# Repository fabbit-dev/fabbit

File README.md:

<h1 align="center">
  <picture>
    <source media="(prefers-color-scheme: dark)" srcset="docs/img/fabbit-logo-dark.png">
    
  </picture>
</h1>

<p align="center">
  Открытый карманный прибор электронщика на ПЛИС, сделанный двумя школьниками.<br>
  Профиль меняет схему прибора.
</p>

<p align="center">

</p>

<p align="center">

</p>

<p align="center">
  <sub>сайт <a href="https://fabbit.dev">fabbit.dev</a></sub>
</p>

## Что это

Fabbit собирает в одном корпусе логический анализатор (ЛА), отладчик, осциллограф,
генератор, мультиметр и лабораторный источник. На экране и по HDMI идут ретро-игры.

Внутри модуль ПЛИС Artix-7. Профиль — битстрим ПЛИС с логикой прибора, его выбирают в меню.

Fabbit для инженеров и исследователей железа. Код, платы и корпус открыты:
свой профиль или свою плату-мезонин может сделать любой.

## Профили из коробки

| Профиль | Что умеет |
|---|---|
| Логический анализатор | Порт A: 16 входов 0–10 В (выдерживают ±30 В), порог 0–6,8 В, входы CK и TRIG. Порт B: 8 двунаправленных линий 1,1–4,7 В. Поток в ПК: 50 MS/s на 16 каналах или 100 MS/s на 8 |
| Отладчик debug & trace | CMSIS-DAP v2: SWD, JTAG, trace 4 бит, разъём MIPI-20 |
| Осциллограф | 2 канала, АЦП HMCAD1511 8 бит, 2 × 312–375 MS/s, 2 × 400 MS/s после подстройки задержек LVDS, щупы ×1/×10 |
| Генератор | ЦАП DAC904 14 бит, 9,6 Впп без нагрузки, 4,8 Впп на 50 Ом. Выход выдерживает ±25 В |
| Мультиметр | АЦП ADS1220 24 бит: напряжение, сопротивление |
| Лабораторный источник | 0,8–22 В с ограничением тока: до 20 Вт от PD-зарядника, до 5 Вт от батареи. Измеряет напряжение, ток, мощность и энергию. При выходе до 5,5 В ток меряет с автодиапазоном 0,2 мкА…3 А |
| Глитчер | Ключ закорачивает питание цели на время, которое задаёт ПЛИС: атаки сбоем питания |
| Ретро-консоль | Ретро-ядра на экране и HDMI, кнопки, звук |

## Железо

| Узел | Параметры |
|---|---|
| ПЛИС | Colorlight i9+ в гнезде SO-DIMM: Artix-7 XC7A50T (32 600 LUT6, 2,7 Мбит BRAM, 120 DSP), SDRAM 8 МБ, флеш 16 МБ |
| Супервизор | WCH CH32H417: меню, microSD, питание и заряд. Параллельная шина UHSIF 16 бит к ПЛИС |
| Экран | IPS 3,5″ 640×480, HDMI с тем же кадром |
| Связь | USB 3.0, 5 Гбит/с. ESP32-C5: Wi-Fi 6 на 2,4 и 5 ГГц, BLE 5, 802.15.4 |
| Питание | USB-C PD 3.1: заряд и отдача 5 В до 1 А. Li-pol 1S, 2800 мА·ч, 3–9 ч работы ([расчёт](journal/2026-10-17.md)) |
| Ввод | 11 кнопок, колесо с нажатием, кнопка питания |
| Периферия | Динамик 1 Вт, микрофон, вибромотор, ИК приём и передача, IMU, RTC, microSD, Qwiic, светодиод состояния |
| Опорная частота | TCXO 25 МГц ±0,5 ppm: шкала времени и частотомер |
| Корпус | 90 × 150 × 22,5 мм, над модулем аналога 24 мм, SLA-печать |

## Как устроено

<picture>
  <source media="(prefers-color-scheme: dark)" srcset="docs/img/fabbit-board-dark.png">
  
</picture>

```mermaid
flowchart TB
  HOST["ПК"]
  subgraph DEV["Fabbit"]
    USBC["USB-C: USB 3.0, PD 3.1"]
    MCU["Супервизор CH32H417<br/>USB, меню, microSD<br/>питание и заряд<br/>Wi-Fi, кнопки, ИК, IMU"]
    FPGA["ПЛИС Artix-7<br/>модуль Colorlight i9+<br/>оболочка + профиль"]
    VID["Экран 3,5″ 640×480<br/>HDMI, звук"]
    IO["ЛА: 16 входов 0–10 В<br/>и 8 линий 1,1–4,7 В<br/>MIPI-20: SWD, JTAG, trace"]
    AMOD["Модуль аналога<br/>осциллограф, генератор<br/>мультиметр"]
    PSU["Лаб. источник 0,8–22 В<br/>глитчер"]
  end
  HOST <-->|"USB 3.0"| USBC
  USBC <--> MCU
  USBC -->|"питание"| PSU
  MCU <-->|"UHSIF 16 бит, JTAG"| FPGA
  MCU -->|"уставки"| PSU
  MCU -->|"SPI, I²C"| AMOD
  FPGA --> VID
  FPGA <--> IO
  FPGA <-->|"LVDS, ЦАП"| AMOD
  FPGA <-->|"диапазоны тока, глитчер"| PSU
```

Поток ЛА и trace идёт из ПЛИС по шине UHSIF в буфер USB 3.0 супервизора без копирования.

| Слой | Что делает |
|---|---|
| Супервизор CH32H417 | Работает всегда. Грузит профили в ПЛИС, ведёт лабораторный источник и мультиметр |
| Оболочка ПЛИС | Общая часть каждого профиля: шина к супервизору, видео на экран и HDMI с меню поверх, SDRAM, UART-мост на порт B, безопасные состояния выводов |
| Профиль | Логика одного прибора поверх оболочки |
| ПО на ПК | sigrok и PulseView, OpenOCD, pyOCD и probe-rs по CMSIS-DAP v2, orbuculum, SCPI, MCP-сервер для ИИ-агентов |

Профиль выбирают в меню golden-загрузчика:

```mermaid
flowchart TB
  ON["Включение"] --> GOLD["Golden-загрузчик<br/>из флеша модуля i9+<br/>меню и экран заряда"]
  GOLD -->|"выбор профиля"| PROF["Профиль из слота флеша<br/>или с microSD"]
  PROF -->|"выход"| GOLD
  GOLD -.->|"сбой"| RESC["Аварийный образ<br/>из флеша супервизора по JTAG"]
```

## Разъёмы

- **Верхний край.** Порт A 2×12 и порт B 2×10 с шагом 2,54 мм, питание цели 2×2, MIPI-20.
- **Разъём мезонина.** BergStak 2×40, шаг 0,8 мм, стек 9 мм. На разъёме 35 линий ПЛИС
  (20 из них в 10 парах LVDS), SPI и I²C супервизора, питание и опорные 25 МГц от TCXO.

## Структура репозитория

```
gateware/            ПЛИС
├── common/          оболочка: шина, видео, SDRAM
├── constraints/     назначение ножек
├── golden/          golden-загрузчик
├── diag/            проверки проводки
├── profiles/        исходники профилей
├── sim/             симуляция
└── tools/           сборка
firmware/            прошивка супервизора
└── ports/esp32s3/   стенд на ESP32-S3
profiles/            содержимое карты microSD
hardware/            платы и корпус
├── mainboard/       главная плата, KiCad 10
├── analog-module/   аналоговый модуль
├── panel-adapter/   переходник дисплея
├── case/            корпус, FreeCAD 1.1 и STL
└── docs/            компоненты (BOM) и проверка по даташитам
host/                ПО для ПК
├── sigrok/          драйвер libsigrok
└── tools/           утилиты
docs/                протокол шины, картинки README
journal/             дневник: замеры и тупики
```

## Команда

&nbsp; **Рома Горбачев**, главный инженер, программист

&nbsp; **Ярик Павлюк**, корпус и 3D

## Как помочь

- Написать свой профиль, сделать свою плату-мезонин, проверить схемы и платы по даташитам.
  Порядок работы: [CONTRIBUTING.md](CONTRIBUTING.md).
- Вопросы и идеи: [Issues](https://github.com/fabbit-dev/fabbit/issues).
- Поддержать проект деньгами: [fabbit.dev/#support](https://fabbit.dev/#support).

Лицензии: код MIT ([LICENSE](LICENSE)), железо CERN-OHL-S-2.0 ([hardware/LICENSE](hardware/LICENSE)).

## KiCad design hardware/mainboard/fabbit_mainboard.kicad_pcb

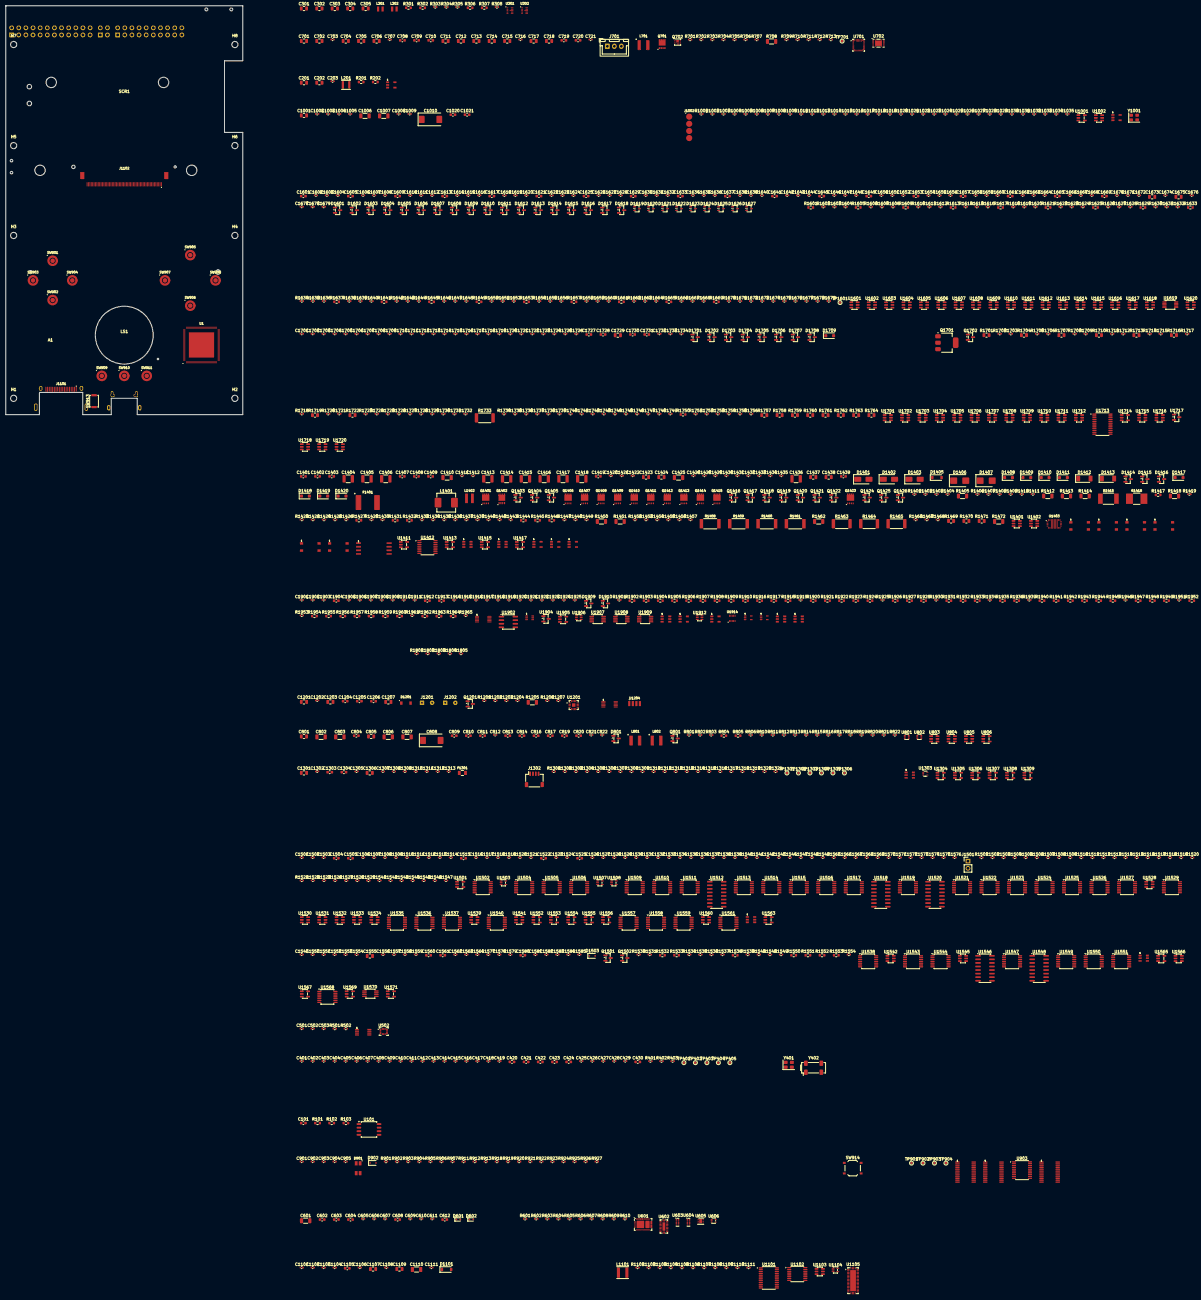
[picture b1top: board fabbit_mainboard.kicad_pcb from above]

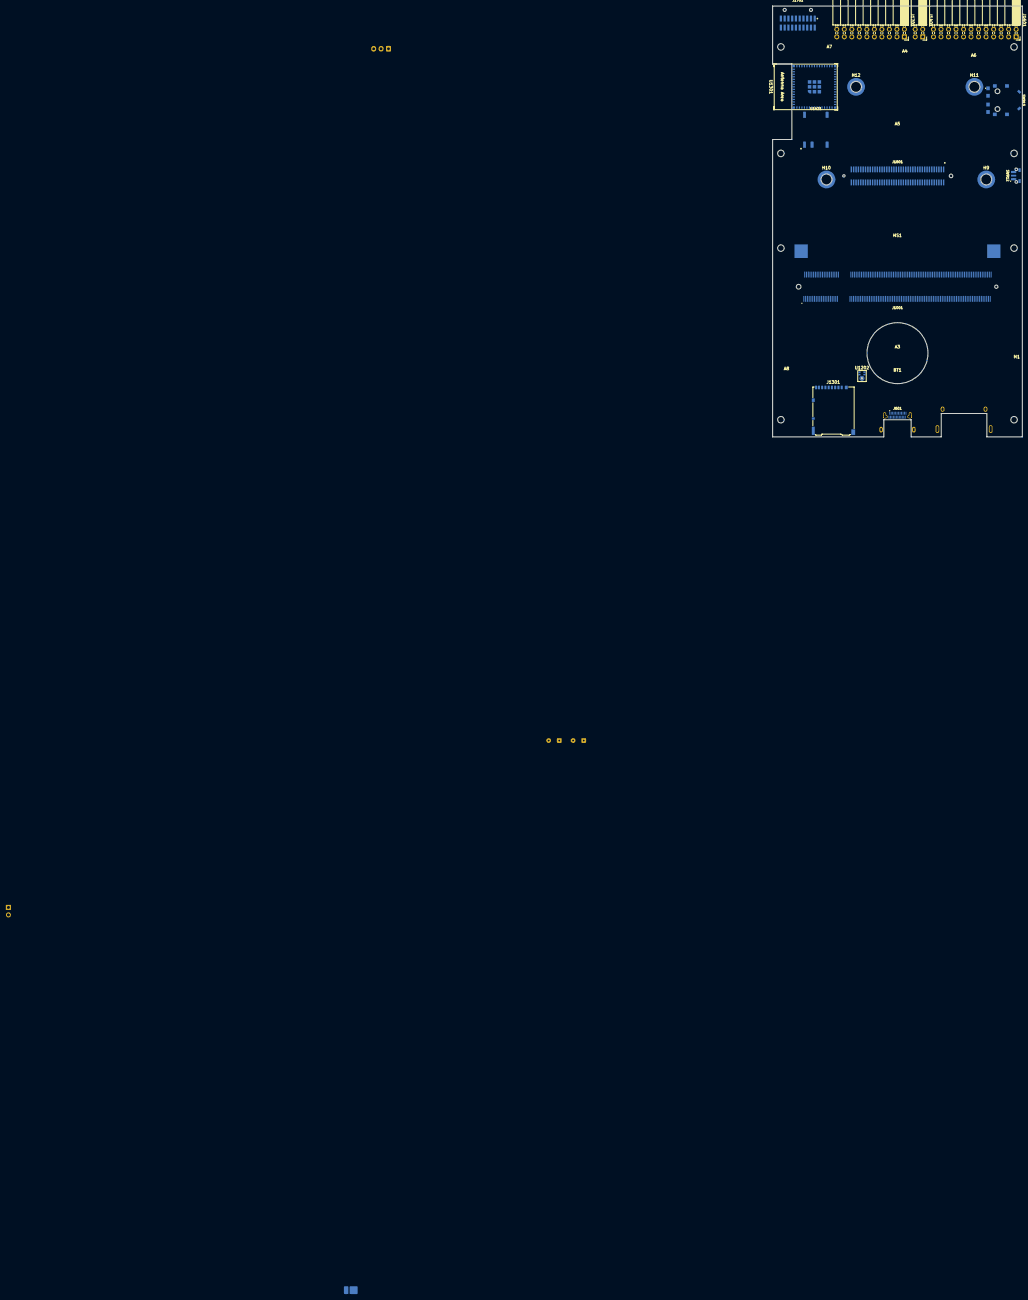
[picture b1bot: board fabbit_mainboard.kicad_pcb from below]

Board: 6 copper layers, 84.4 x 145.6 mm, 1260 parts (26 on the bottom side), 865 nets, no tracks yet.

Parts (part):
A1: MECH_Area_F_Power_27.4x17
A3: MECH_Area_B_Low_68x23.7
A4: MECH_Area_B_Scoop_25x10.6
A5: MECH_Area_B_LabPSU_28x13.5
A6: MECH_Area_B_Anlz_A_21.5x13.4
A7: MECH_Area_B_Anlz_B_22x7.6
A8: MECH_Battery_Tail_5x18
BT1: MECH_Battery_70x40
C101: 100n X7R; C_0603_1608Metric
C201: 10uF 25V X5R 0805; C_0805_2012Metric
C202: 22uF 25V X5R 0805; C_0805_2012Metric
C203: 6.8pF 50V C0G 0402; C_0402_1005Metric
C301, C303, C305, C711, C712, C713, C714, C715, C717, C718, C801, C805, C1001, C1107, C1201, C1207, C1306, C1673, C1675: 10uF 10V X5R 0805; C_0805_2012Metric
C302, C304, C1301: 22uF 10V X5R 0805; C_0805_2012Metric
C401, C402, C403, C404, C405, C406, C407, C408, C409, C410, C411, C412, C413, C414, C415, C416, C417, C418, C419, C429: 100nF; C_0402_1005Metric
C420, C421: 10uF; C_0603_1608Metric
C422, C423, C424: 2.2uF; C_0603_1608Metric
C425, C426, C427, C428: 15pF; C_0402_1005Metric
C430, C810, C811, C813, C814, C816, C817, C819, C820, C1403, C1727, C1731: 1uF 10V X7R 0603; C_0603_1608Metric
C501, C502, C503, C611, C822, C901, C902, C903, C904, C905, C1501, C1502, C1503, C1506, C1507, C1508, C1509, C1510, C1511, C1512, C1513, C1514, C1516, C1517, C1518, C1519, C1520, C1521, C1523, C1524, C1526, C1527, C1528, C1529, C1530, C1531, C1532, C1533, C1534, C1535, C1536, C1537, C1538, C1539, C1540, C1541, C1543, C1544, C1545, C1547, C1548, C1549, C1550, C1551, C1553, C1554, C1556, C1557, C1558, C1559, C1562, C1564, C1565, C1566, C1567, C1568, C1569, C1570, C1571, C1572, C1573, C1574, C1575, C1576, C1577, C1578, C1579, C1581, C1582, C1583, C1584, C1585, C1679: 100nF X7R 16V 0402; C_0402_1005Metric
C601: 4.7uF 50V X7R 1206; C_1206_3216Metric
C602, C603, C608: 10uF 10V X5R 0603; C_0603_1608Metric
C604: 10uF 6.3V X5R 0603; C_0603_1608Metric
C605, C606, C1908, C1909: 330pF 50V C0G 0402; C_0402_1005Metric
C607, C609, C610, C716, C721, C821, C1002, C1004, C1005, C1008, C1009, C1101, C1102, C1103, C1104, C1108, C1111, C1202, C1302, C1307, C1308, C1309, C1310, C1311, C1312, C1313, C1421, C1422, C1428, C1429, C1432, C1433, C1434, C1435, C1603, C1607, C1611, C1615, C1619, C1623, C1627, C1631, C1635, C1639, C1643, C1647, C1651, C1655, C1659, C1663, C1667, C1671, C1674, C1676, C1677, C1678, C1701, C1702, C1703, C1704, C1705, C1706, C1707, C1708, C1709, C1710, C1711, C1712, C1713, C1714, C1715, C1716, C1717, C1718, C1719, C1720, C1721, C1722, C1723, C1724, C1725, C1726, C1733, C1734, C1901, C1902, C1903, C1905, C1906, C1907, C1910, C1911, C1916, C1917, C1918, C1919, C1920, C1921, C1922, C1923: 100nF 16V X7R 0402; C_0402_1005Metric
C612, C1730, C1904: 10nF 50V C0G 0603; C_0603_1608Metric
C701, C702, C704, C705, C706: 10uF 35V X5R 0805; C_0805_2012Metric
C703, C707: 100nF 50V X7R 0402; C_0402_1005Metric
C708, C1206: 4.7uF 10V X5R 0603; C_0603_1608Metric
C709, C710: 47nF 25V X7R 0603; C_0603_1608Metric
C719, C1105, C1204, C1205, C1303, C1304: 1uF 10V X5R 0603; C_0603_1608Metric
C720: 470nF 10V X5R 0603; C_0603_1608Metric
C802, C803, C806, C807: 22uF 16V X5R 1206; C_1206_3216Metric
C804: 1.5nF 50V C0G 0603; C_0603_1608Metric
C808: 150uF 10V polymer ESR15m; CP_EIA-7343-31_Kemet-D
C809: 1.8nF 50V C0G 0603; C_0603_1608Metric
C812, C1732: 1nF 50V X7R 0402; C_0402_1005Metric
C1003, C1604, C1608, C1612, C1616, C1620, C1624, C1628, C1632, C1636, C1640, C1644, C1648, C1652, C1656, C1660, C1664, C1668, C1672: 10nF 50V X7R 0402; C_0402_1005Metric
C1006, C1007: 22uF 25V X7R 1206; C_1206_3216Metric
C1010: 47uF 10V polymer; CP_EIA-7343-31_Kemet-D
C1020, C1021, C1728: 2.2uF 10V X7R 0603; C_0603_1608Metric
C1106, C1305, C1420, C1914: 1nF 50V C0G 0402; C_0402_1005Metric
C1109, C1424: 4.7uF 10V X5R 0805; C_0805_2012Metric
C1110: 2.2uF 50V X7R 1206; C_1206_3216Metric
C1203: 100nF 16V C0G 0805; C_0805_2012Metric
C1401, C1408, C1409: 100nF 25V X7R 0603; C_0603_1608Metric
C1402, C1407, C1419: 100nF 50V X7R 0603; C_0603_1608Metric
C1404, C1405, C1406, C1413, C1414, C1415, C1416, C1417, C1418: 10uF 50V X7R 1210 GRM32ER71H106KA12L; C_1210_3225Metric
C1410: 10uF 16V X7R 1206; C_1206_3216Metric
C1411: 15nF 50V X7R 0402; C_0402_1005Metric
C1412: 47pF 50V C0G 0402; C_0402_1005Metric
C1423: 1uF 35V X7R 0805; C_0805_2012Metric
C1425: 4.7uF 25V X7R 1206; C_1206_3216Metric
C1426: 820pF 50V C0G 0402; C_0402_1005Metric
C1430, C1431, C1924, C1925: 100nF 10V X7R 0402; C_0402_1005Metric
C1436: 10uF 35V X7R 1210; C_1210_3225Metric
C1437: 2.2uF 25V X7R 0805; C_0805_2012Metric
C1438: 2.2uF 35V X7R 0805; C_0805_2012Metric
C1439: 100nF 35V X7R 0603; C_0603_1608Metric
C1504, C1505: 220nF X7R 16V 0603; C_0603_1608Metric
C1515, C1522, C1525, C1560: 10nF_PENDING 5% C0G 50V 0603; C_0603_1608Metric
C1542: 10nF X7R 16V 0402; C_0402_1005Metric
C1552: 1nF_PENDING C0G 50V 0402; C_0402_1005Metric
C1555: 2.2uF 20% X7R 16V 0805; C_0805_2012Metric
C1561: 10nF 5% C0G 50V 0603; C_0603_1608Metric
C1563: 1nF 5% C0G 50V 0402; C_0402_1005Metric
C1580, C1912, C1913: 10nF 5% C0G 30ppm/K 50V 0603; C_0603_1608Metric
C1601, C1605, C1609, C1613, C1617, C1621, C1625, C1629, C1633, C1637, C1641, C1645, C1649, C1653, C1657, C1661, C1665, C1669: 2.2pF ±0.1pF C0G 50V 0603; C_0603_1608Metric
C1602, C1606, C1610, C1614, C1618, C1622, C1626, C1630, C1634, C1638, C1642, C1646, C1650, C1654, C1658, C1662, C1666, C1670: DNP 12pF C0G 50V 0402; C_0402_1005Metric
C1729: 1uF 16V X7R 0805; C_0805_2012Metric
C1915: 10nF 25V X7R 0402; C_0402_1005Metric
D601, D602: ESD751DYAR; D_SOD-523
D801: BAT54C; SOT-23
D901: LTST-C155KGJRKT; LiteOn_LTST-C155_3.2x2.7mm
D902, D1503: 1N4148WS; D_SOD-323
D1101: B5819W 40V 1A SOD-123; D_SOD-123
D1201: VSMB2943SLX01; Vishay_VSMB2943SLX01
D1401: S1J; D_SMA
D1402, D1403: SMAJ13CA-TR; D_SMA
D1405: MBR0530T1G; D_SOD-123
D1406, D1407: SMBJ15CA; D_SMB
D1408, D1417, D1418, D1419, D1420: BZT52H-C12,115; D_SOD-123F
D1409, D1410, D1411: BZT52H-C5V1,115; D_SOD-123F
D1412, D1413: PMEG4050EP,115; D_SOD-128
D1414, D1415, D1416, D1601, D1602, D1603, D1604, D1605, D1606, D1607, D1608, D1609, D1610, D1611, D1612, D1613, D1614, D1615, D1616, D1617, D1618, D1909, D1910: BAV199LT1G; SOT-23
D1619, D1620, D1621, D1622, D1623, D1624, D1625, D1626, D1627: ESDCAN05-2BWY; SOT-323_SC-70
D1701, D1702, D1703, D1704, D1705, D1706, D1707, D1708: BAV99,215; SOT-23
D1709: SMF7.0A; D_SOD-123F
F1301: MF-PSMF020X-2 PTC 0.2A hold 9V 0805; Fuse_Bourns_MF-PSMF_0805
F1401: 2920L500/30GR 30V 5A; Fuse_LUTE_2920L
H1, H2, H3, H4, H5, H6, H7, H8: MountingHole_2.2mm_M2
H9, H10, H11, H12: Mounting_Wuerth_WA-SMSI-M2.5_H9mm_9774090151
HS1: MECH_Heat_Spreader_23x22
J601: HC-TYPE-C-24P-MM0.8-5A-01; USB_C_HCTL_HC-TYPE-C-24P-MM0.8-5A
J701: B3B-XH-A(LF)(SN); JST_XH_B3B-XH-A_1x03_P2.50mm_Vertical
J1001: 1473005-4; SODIMM_TE_1473005-4_200P_P0.6mm
J1002: JTAG pogo J5/J4/J3/J2; Pogo_YTC1P-2510_1x04_P2.54mm
J1101: GT-HD002A-FNNG1; HDMI_A_G-Switch_GT-HD002A_MidMount
J1102: FC-05B54P21H20; FPC_BXCONN_FC-05B54P21H20_1x54_P0.5mm
J1201: Speaker 8R 1W; SolderWire-0.1sqmm_1x02_P3.6mm_D0.4mm_OD1mm
J1202: LRA; SolderWire-0.1sqmm_1x02_P3.6mm_D0.4mm_OD1mm
J1301: DM3AT-SF-PEJM5; microSD_HC_Hirose_DM3AT-SF-PEJM5
J1302: SM04B-SRSS-TB(LF)(SN); JST_SH_SM04B-SRSS-TB_1x04-1MP_P1.00mm_Horizontal
J1401: DS1024-2x2R2; PinSocket_2x02_P2.54mm_Horizontal
J1501: LAB jumper; PinHeader_1x02_P2.54mm_Vertical
J1601: DS1024-2x12R2; PinSocket_2x12_P2.54mm_Horizontal
J1701: B 2x10 PENDING; PinSocket_2x10_P2.54mm_Horizontal
J1702: FTSH-110-01-L-DH-A; Samtec_FTSH-110-01-x-DH-A_2x10_P1.27mm_Horizontal_SMD
J1801: 61082-082402LF; Amphenol_BergStak_61082-08xx_2x40_P0.8mm_Receptacle
L201: 2.2uH; L_Sunlord_SWPA3015S
L301, L302: 0.47uH DFE201612E-R47M; L_Murata_DFE201612E
L701: 2.2uH PNR4020-2R2M; L_APV_PNR4020
L801, L802: 1uH PNR4020-1R0M; L_APV_PNR4020
L1101: 4.7uH 2.2A SWPA4018S4R7MT; L_Sunlord_SWPA4018S
L1401: 3.3uH 13.5A IHLP2525CZER3R3M01; L_Vishay_IHLP-2525
L1402: 10uH 20% VLS3012HBX-100M; L_TDK_VLS3012HBX
LS1: MECH_Speaker_D20
M1: MECH_LRA_12x3.4
Q701: CSD17308Q3; TI_CSD_SON-8_3.3x3.3_Q3
Q702: CSD13202Q2; Texas_DQK
Q801, Q1403, Q1424, Q1425, Q1426, Q1501, Q1502: PMV40UN2R; SOT-23
Q1201: AO3400A; SOT-23
Q1401, Q1406, Q1407, Q1408, Q1409, Q1410, Q1411, Q1412, Q1413, Q1414, Q1415, Q1423: PXN012-60QLJ; Nexperia_MLPAK33_SOT8002-1
Q1402: AONR21357; AOS_DFN-8-1EP_3x3mm_P0.65mm_AONR
Q1404, Q1405, Q1702: 2N7002; SOT-23
Q1416, Q1417, Q1418, Q1419, Q1421, Q1422: 2N7002,215; SOT-23
Q1420: PMV65XP,215; SOT-23
Q1701: BCP53-16,115; SOT-223
R101, R102, R103: 10k; R_0603_1608Metric
R201: 105k 0.1%; R_0603_1608Metric
R202: 100k 0.1%; R_0603_1608Metric
R301, R306: 255k 0.1% 25ppm 0603; R_0603_1608Metric
R302, R307: 45.3k 0.1% 25ppm 0603; R_0603_1608Metric
R303, R603, R604, R605, R606, R703, R707, R709, R710, R817, R901, R902, R903, R904, R905, R907, R911, R918, R919, R920, R921, R922, R923, R924, R925, R926, R927, R1101, R1102, R1104, R1105, R1109, R1110, R1111, R1302, R1303, R1304, R1305, R1442, R1447, R1503, R1505, R1507, R1508, R1509, R1517, R1519, R1520, R1521, R1522, R1523, R1531, R1536, R1537, R1547, R1548, R1554, R1674, R1677, R1678, R1679, R1731, R1802, R1805, R1919, R1925, R1930, R1934, R1939, R1951, R1953, R1961: 10k 1% 0402; R_0402_1005Metric
R304: 196k 1% 0402; R_0402_1005Metric
R305, R801: 102k 1% 0402; R_0402_1005Metric
R308, R713, R803, R806, R810, R811, R812, R813, R814, R815, R816, R818, R820, R906, R1103, R1107, R1108, R1202, R1207, R1311, R1315, R1316, R1317, R1318, R1319, R1320, R1321, R1401, R1404, R1409, R1410, R1411, R1428, R1430, R1433, R1439, R1440, R1443, R1454, R1455, R1466, R1467, R1468, R1511, R1526, R1527, R1528, R1529, R1546, R1549, R1734, R1737, R1738, R1739, R1747, R1748, R1749, R1751, R1752, R1753, R1754, R1755, R1756, R1801, R1803, R1804: 100k 1% 0402; R_0402_1005Metric
R401: 10kOhm; R_0402_1005Metric
R402: 1kOhm; R_0402_1005Metric
R403, R1001, R1965: 10R 1% 0402; R_0402_1005Metric
R501, R502, R1008, R1009, R1313, R1314, R1420, R1425, R1448, R1449, R1725, R1726, R1727, R1728, R1729, R1740, R1741: 2.2k 1% 0402; R_0402_1005Metric
R601, R607, R608, R1407: 20k 1% 0402; R_0402_1005Metric
R602, R1301, R1501, R1540, R1732: 1k 1% 0402; R_0402_1005Metric
R609, R1512: 200k 1% 0402; R_0402_1005Metric
R610: 2.00k 1% 0402; R_0402_1005Metric
R701, R1419, R1424, R1541, R1542, R1543, R1544, R1545, R1702, R1705, R1708, R1711, R1714, R1717, R1720, R1723: 4.7k 1% 0402; R_0402_1005Metric
R702: 26.7k 1% 0402; R_0402_1005Metric
R704, R1011, R1012, R1013, R1014, R1015, R1016, R1017, R1018, R1019, R1020, R1204, R1206, R1434, R1435, R1436, R1437, R1452, R1453: 100R 1% 0402; R_0402_1005Metric
R705: TS_RT1_PENDING 1% 0402; R_0402_1005Metric
R706: TS_RT2_PENDING 1% 0402; R_0402_1005Metric
R708: 10mR 1% 1W 1206; R_1206_3216Metric
R711, R712, R1002: 1M 1% 0402; R_0402_1005Metric
R802: 13.7k 1% 0402; R_0402_1005Metric
R804: 82.5k 0.1% 25ppm 0603; R_0603_1608Metric
R805: 10.7k 0.1% 25ppm 0603; R_0603_1608Metric
R819, R1408: 68.1k 1% 0402; R_0402_1005Metric
R821: 59k 1% 0402; R_0402_1005Metric
R822: 23.7k 1% 0402; R_0402_1005Metric
R912, R913: 680R 1% 0402; R_0402_1005Metric
R1003, R1004, R1005, R1006, R1007, R1021, R1022, R1023, R1024, R1025, R1026, R1027, R1028, R1029, R1030, R1031, R1032, R1033, R1034, R1035, R1312, R1421, R1426, R1604, R1608, R1612, R1616, R1620, R1624, R1628, R1632, R1636, R1640, R1644, R1648, R1652, R1656, R1660, R1664, R1668, R1672, R1742, R1743, R1744, R1745: 33R 1% 0402; R_0402_1005Metric
R1106: 10.2 1% 0402; R_0402_1005Metric
R1201: 634k 1% 0402; R_0402_1005Metric
R1203, R1673: 1.2k 1% 0402; R_0402_1005Metric
R1205: 39R 1% 1206 0.5W; R_1206_3216Metric
R1306, R1307, R1308, R1309, R1310, R1504, R1506, R1518: 47k 1% 0402; R_0402_1005Metric
R1402: 39.2k 1% 0402; R_0402_1005Metric
R1403: 29.4k 1% 0402; R_0402_1005Metric
R1405: 20mR 1% 1W 1206 ERJ-8CWFR020V; R_1206_3216Metric
R1406: 40.2k 1% 0402; R_0402_1005Metric
R1412, R1413, R1414, R1418, R1450, R1451: 100R 1% 0.5W 1206; R_1206_3216Metric
R1415: 10mR 1% 1W 2512 WSL2512R0100FEA; R_Vishay_WSL2512_7m-500m
R1416: 1R 1% 100ppm/K 2W 2512 CRM2512-FX-1R00ELF; R_Bourns_CRM2512
R1417: 100R 0.1% 25ppm 0603 RT0603BRD07100RL; R_0603_1608Metric
R1427, R1954, R1955: 10R 1% 0603; R_0603_1608Metric
R1431: 86.6k 0.1% 10ppm/K 0603; R_0603_1608Metric
R1432, R1963: 10.0k 0.1% 10ppm/K 0603; R_0603_1608Metric
R1444: 1k 1% 0.1W 0603; R_0603_1608Metric
R1445: 698k 0.1% 10ppm/K 0603; R_0603_1608Metric
R1446, R1931, R1941, R1942, R1944, R1945: 100k 0.1% 10ppm/K 0603; R_0603_1608Metric
R1456, R1457: 10M 1% 0402; R_0402_1005Metric
R1458, R1459, R1460, R1461: 4.02R 1% 100ppm/K 1.5W 2512 CRCW25124R02FKEGHP; R_Vishay_CRCW2512-HP
R1462, R1472: 1.00k 1% 100ppm/K 0.5W 1206; R_1206_3216Metric
R1463, R1464, R1465: 1.00k 1% 1W 2512; R_2512_6332Metric
R1469, R1470, R1471: 100R 1% 0.25W 0805; R_0805_2012Metric
R1502, R1510, R1530, R1539: 1.5k 1% 0402; R_0402_1005Metric
R1513, R1515: 68k 1% 0402; R_0402_1005Metric
R1514, R1516: 136k 1% 0402; R_0402_1005Metric
R1532: 270R 1% 100ppm/K 0603; R_0603_1608Metric
R1533: 22k 1% 100ppm/K 0603; R_0603_1608Metric
R1534, R1746: 150k 1% 0402; R_0402_1005Metric
R1535: 300k 1% 0402; R_0402_1005Metric
R1538: 220R 1% 0603; R_0603_1608Metric
R1550: 221R 1% 100ppm/K 0603; R_0603_1608Metric
R1551: 2.2k 1% 100ppm/K 0603; R_0603_1608Metric
R1552, R1921, R1952: 10k 0.1% 10ppm/K 0603; R_0603_1608Metric
R1553: 1.50k 0.1% 10ppm/K 0603; R_0603_1608Metric
R1601, R1605, R1609, R1613, R1617, R1621, R1625, R1629, R1633, R1637, R1641, R1645, R1649, R1653, R1657, R1661, R1665, R1669: 174k 1% 0603 75V; R_0603_1608Metric
R1602, R1606, R1610, R1614, R1618, R1622, R1626, R1630, R1634, R1638, R1642, R1646, R1650, R1654, R1658, R1662, R1666, R1670: 75.0k 1% 0402; R_0402_1005Metric
R1603, R1607, R1611, R1615, R1619, R1623, R1627, R1631, R1635, R1639, R1643, R1647, R1651, R1655, R1659, R1663, R1667, R1671: DNP 10M 1% 0402; R_0402_1005Metric
R1675, R1676: 330R 1% 0402; R_0402_1005Metric
R1701, R1704, R1707, R1710, R1713, R1716, R1719, R1722, R1757, R1758, R1759, R1760, R1761, R1762, R1763, R1764: 100R 1% 0805 CRCW-HP 0.5W; R_0805_2012Metric
R1703, R1706, R1709, R1712, R1715, R1718, R1721, R1724: 220k 1% 0402; R_0402_1005Metric
R1730: 31.6k 1% 0402; R_0402_1005Metric
R1733: 6.8R 1% 2512 1W; R_2512_6332Metric
R1735: 17.4k 1% 0402; R_0402_1005Metric
R1736: 56.2k 1% 0402; R_0402_1005Metric
R1750: 1k 1% 0603; R_0603_1608Metric
R1901: 1.30k 1% 0402; R_0402_1005Metric
R1902: 1.0k 0.1% 10ppm/K 0603; R_0603_1608Metric
R1903: 357R 0.1% 10ppm/K 0603; R_0603_1608Metric
R1904: 649R 0.1% 10ppm/K 0603; R_0603_1608Metric
R1905: 7.15k 0.1% 0603; R_0603_1608Metric
R1906: 1.0k 0.1% 0603; R_0603_1608Metric
R1907, R1909: 6.81k 0.1% 0603; R_0603_1608Metric
R1908, R1910: 2.94k 0.1% 0603; R_0603_1608Metric
R1916, R1920: 200k 0.1% 10ppm/K 0603; R_0603_1608Metric
R1917, R1922: 54.9k 0.1% 10ppm/K 0603; R_0603_1608Metric
R1918, R1924: 4.7M 1% 100ppm/K 0603; R_0603_1608Metric
R1923: 10k 1% 100ppm/K 0603; R_0603_1608Metric
R1926, R1927, R1940, R1943, R1947, R1948: 1.00M 0.1% 10ppm/K 0603; R_0603_1608Metric
R1928, R1949: 18.0k 0.1% 10ppm/K 0603; R_0603_1608Metric
R1932: 6.34k 0.1% 10ppm/K 0603; R_0603_1608Metric
R1933: 1M 1% 100ppm/K 0603; R_0603_1608Metric
R1935, R1959: 20.0k 0.1% 10ppm/K 0603; R_0603_1608Metric
R1936: 2.30k 0.1% 10ppm/K 0603; R_0603_1608Metric
R1946: 0R 0402; R_0402_1005Metric
R1956: 10k 1% 0603; R_0603_1608Metric
R1957, R1958: 100R 1% 0603; R_0603_1608Metric
R1960: 1.87k 0.1% 10ppm/K 0603; R_0603_1608Metric
R1962: 150k 1% 100ppm/K 0603; R_0603_1608Metric
R1964: 90.5R 0.1% 10ppm/K 0603; R_0603_1608Metric
SCR1: MECH_Screen_70x51
SW901: Up; Dome_Contact_D3.8mm
SW902: Down; Dome_Contact_D3.8mm
SW903: Left; Dome_Contact_D3.8mm
SW904: Right; Dome_Contact_D3.8mm
SW905: F1; Dome_Contact_D3.8mm
SW906: F3; Dome_Contact_D3.8mm
SW907: F4; Dome_Contact_D3.8mm
SW908: F2; Dome_Contact_D3.8mm
SW909: Fn; Dome_Contact_D3.8mm
SW910: Menu; Dome_Contact_D3.8mm
SW911: Back; Dome_Contact_D3.8mm
SW912: Power; SW_Alps_SKRTLAE010_SidePush
SW913: Recovery; SW_Push_SPST_NO_Alps_SKRK
SW914: RESET; SW_Push_1P1T_XKB_TS-1187A
SW915: SIQ-02FVS3; Encoder_Mitsumi_SIQ-02FVS3
TP401: MCU_VDD33_VTREF_SENSE_ONLY; TestPoint_Pad_D1.0mm
TP402: SWCLK_USBHS_DP; TestPoint_Pad_D1.0mm
TP403: SWIO_SWDIO_USBHS_DM; TestPoint_Pad_D1.0mm
TP404: NRST; TestPoint_Pad_D1.0mm
TP405, TP904, TP1306: GND; TestPoint_Pad_D1.0mm
TP701: STAT; TestPoint_Pad_D1.0mm
TP901: V003_SWIO; TestPoint_Pad_D1.0mm
TP902: V003_NRST; TestPoint_Pad_D1.0mm
TP903: 3V3_AON; TestPoint_Pad_D1.0mm
TP1301: ESP_IO13_USB_DM; TestPoint_Pad_D1.0mm
TP1302: ESP_IO14_USB_DP; TestPoint_Pad_D1.0mm
TP1303: ESP_EN; TestPoint_Pad_D1.0mm
TP1304: ESP_IO28; TestPoint_Pad_D1.0mm
TP1305: ESP_3V3; TestPoint_Pad_D1.0mm
TP1601: LDAC; TestPoint_Pad_D1.0mm
U1: CH32H417QEU6; WCH_QFN-128-1EP_12.3x12.3mm_P0.35mm_EP9x9mm
U101: W25Q128JVSIQ; SOIC-8_5.3x5.3mm_P1.27mm
U201: TLV62569DBVR; TI_DBV0005A
U301, U302: TPS63802DLAR; TI_DLA0010A
U501: TMP1075DGKR; TI_DGK0008A
U502: LSM6DS3TR-C; LGA-14_3x2.5mm_P0.5mm_LayoutBorder3x4y
U601: TPS25751DREFR; TI_REF0038A_WQFN-38-2EP_NoVia
U602: HD3SS3212IRKSR; DHVQFN-20-1EP_2.5x4.5mm_P0.5mm_EP1x3mm
U603, U604: TPD4E05U06DQAR; USON-10_2.5x1.0mm_P0.5mm
U605: TVS2200DRVR; WSON-6-1EP_2x2mm_P0.65mm_EP1x1.6mm
U606: TPD2E2U06DRLR; SOT-553
U701: BQ25798RQMR; Texas_RQM0029A_VQFN-29_4x4mm_P0.4mm
U702: BQ27441DRZR-G1A; TI_DRZ0012A_VSON-12_NoVia
U801, U802: TPS61023DRLR; SOT-563
U803, U1103, U1715, U1716: TPS22917DBVR; SOT-23-6
U804, U805: TPS2553DBVR; SOT-23-6
U806: TPS7A0230PDBVR; SOT-23-5
U901, U902, U904: TCA9535PWR; TI_PW0024A
U903: CH32V003F4P6; TSSOP-20_4.4x6.5mm_P0.65mm
U1001: SN74LVC1GU04DBVR; SOT-23-5
U1002: SN74LVC2G34DBVR; SOT-23-6
U1004: TPS7A2033PDBVR; TI_DBV0005A
U1101: TPD12S016PWR; TSSOP-24_4.4x7.8mm_P0.65mm
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
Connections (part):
3V3_AON: C101.1, C201.1, C302.1, C401.1, C404.1, C405.1, C407.1, C408.1, C409.1, C410.1, C411.1, C413.1, C414.1, C415.1, C416.1, C417.1, C419.1, C420.1, C421.1, C422.1, C501.1, C502.1, C503.1, C602.1, C607.1, C608.1, C612.1, C810.1, C812.1, C813.1, C901.1, C902.1, C903.1, C905.1, C1101.1, C1104.1, C1105.1, C1106.1, C1203.1, C1304.1, C1305.1, C1421.1, C1422.1, C1428.1, C1429.1, C1432.1, C1433.1, C1434.1, C1435.1, C1501.1, C1502.1, C1503.1, C1506.1, C1507.1, C1508.1, C1509.1, C1510.1, C1511.1, C1512.1, C1513.1, C1514.1, C1516.1, C1517.1, C1518.1, C1519.1, C1520.1, C1521.1, C1523.1, C1524.1, C1526.1, C1527.1, C1528.1, C1529.1, C1531.1, C1532.1, C1533.1, C1534.1, C1535.1, C1536.1, C1537.1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
3V3_CLK: C1004.1, C1005.1, C1021.1, C1111.1, R1001.1, R1109.1, R1110.1, U1001.5, U1002.5, U1004.5, U1105.1
3V3_LA_IO: C811.1, C1603.1, C1607.1, C1611.1, C1615.1, C1619.1, C1623.1, C1627.1, C1631.1, C1635.1, C1639.1, C1643.1, C1647.1, C1651.1, C1655.1, C1659.1, C1663.1, C1667.1, C1671.1, C1673.1, C1701.1, C1702.1, C1703.1, C1704.1, C1705.1, C1706.1, C1707.1, C1708.1, C1717.1, C1718.1, C1719.1, C1720.1, C1725.1, D1601.2, D1602.2, D1603.2, D1604.2, D1605.2, D1606.2, D1607.2, D1608.2, D1609.2, D1610.2, D1611.2, D1612.2, D1613.2, D1614.2, D1615.2, D1616.2, D1617.2, D1618.2, R1673.1, R1674.1, U803.5, U803.6, U1601.4, U1602.4, U1603.4, U1604.4, U1605.4, U1606.4, U1607.4, U1608.4, U1609.4, U1610.4, U1611.4, U1612.4, U1613.4, U1614.4, U1615.4, U1616.4, U1617.4, U1618.4, U1701.1, U1702.1, U1703.1, U1704.1, U1705.1, U1706.1, U1707.1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
3V3_RF: C304.1, C305.1, C1301.1, C1302.1, C1308.1, C1309.1, C1310.1, C1311.1, C1312.1, C1313.1, R306.1, R1303.1, R1304.1, R1305.1, R1321.1, TP1305.1, U302.6, U1301.3, U1304.5, U1305.5, U1306.5, U1307.5, U1308.5, U1309.5
5V_FPGA: C802.1, C803.1, C804.1, C1006.1, C1007.1, C1008.1, C1009.1, C1010.1, C1020.1, C1102.1, C1727.1, J1001.2, J1001.4, J1001.6, J1001.8, J1001.10, J1001.12, R801.1, R810.1, R1750.1, U801.6, U1004.1, U1004.3, U1101.11, U1714.1
/AON converter draft/AON_EN: R304.2, R305.1, U301.1
/AON converter draft/AON_FB: R301.2, R302.1, U301.4
/AON converter draft/AON_L1: L301.1, U301.9
/AON converter draft/AON_L2: L301.2, U301.7
/AON converter draft/RF_FB: R306.2, R307.1, U302.4
/AON converter draft/RF_L1: L302.1, U302.9
/AON converter draft/RF_L2: L302.2, U302.7
/Charger and battery/BQ_BAT: C717.1, C718.1, Q701.1, Q701.2, Q701.3, U701.22, U701.23
/Charger and battery/BQ_BATP: R704.2, U701.18
/Charger and battery/BQ_BTST1: C709.1, U701.4
/Charger and battery/BQ_BTST2: C710.1, U701.19
/Charger and battery/BQ_ILIM: R702.2, R703.1, U701.17
/Charger and battery/BQ_PMID: C704.1, C705.1, C706.1, C707.1, U701.29
/Charger and battery/BQ_PROG: R701.1, U701.20
/Charger and battery/BQ_REGN: C708.1, R702.1, R705.1, U701.5
/Charger and battery/BQ_STAT: R707.2, TP701.1, U701.1
/Charger and battery/BQ_SW1: C709.2, L701.1, U701.28
/Charger and battery/BQ_SW2: C710.2, L701.2, U701.26
/Charger and battery/BQ_TS: J701.3, R705.2, R706.1, U701.16
/Charger and battery/GAUGE_BIN: R709.1, U702.10
/Charger and battery/GAUGE_GPOUT: R710.2, U702.12
/Charger and battery/GAUGE_VDD: C720.1, R710.1, U702.5
/Charger and battery/PACKP: C719.1, J701.1, R704.1, R708.1, U702.6, U702.8
/Charger and battery/SFET_GATE: Q701.4, U701.24
/Core converter draft/CORE_FB: C203.2, R201.2, R202.1, U201.5
/Core converter draft/CORE_SW: L201.1, U201.3
/FPGA module/CLK_BIAS: C1003.2, R1002.1, U1001.2
/FPGA module/CLK_SQ: R1002.2, U1001.4, U1002.1, U1002.3
/FPGA module/DAC_CLK_FPGA: J1001.102, R1035.1
/FPGA module/DAC_D0_FPGA: J1001.42, R1021.1
/FPGA module/DAC_D1_FPGA: J1001.68, R1022.1
/FPGA module/DAC_D2_FPGA: J1001.64, R1023.1
/FPGA module/DAC_D3_FPGA: J1001.66, R1024.1
/FPGA module/DAC_D4_FPGA: J1001.72, R1025.1
/FPGA module/DAC_D5_FPGA: J1001.74, R1026.1
/FPGA module/DAC_D6_FPGA: J1001.76, R1027.1
/FPGA module/DAC_D7_FPGA: J1001.78, R1028.1
/FPGA module/DAC_D8_FPGA: J1001.80, R1029.1
/FPGA module/DAC_D9_FPGA: J1001.82, R1030.1
/FPGA module/DAC_D10_FPGA: J1001.86, R1031.1
/FPGA module/DAC_D11_FPGA: J1001.94, R1032.1
/FPGA module/DAC_D12_FPGA: J1001.96, R1033.1
/FPGA module/DAC_D13_FPGA: J1001.100, R1034.1
/FPGA module/JTAG_TCK_MOD: J1002.1, R1005.2
/FPGA module/JTAG_TDI_MOD: J1002.3, R1007.2
/FPGA module/JTAG_TMS_MOD: J1002.2, R1006.2
/FPGA module/REF_25M_FPGA: J1001.58, R1003.2
/FPGA module/REF_25M_FPGA_SRC: R1003.1, U1002.6
/FPGA module/REF_25M_MEZZ_SRC: R1004.1, U1002.4
/FPGA module/TCXO_OUT: C1003.1, Y1001.3
/FPGA module/TCXO_VCC: C1001.1, C1002.1, R1001.2, Y1001.4
/LA port A/LA_A0_CMP: R1603.2, R1604.1, U1601.5
/LA port A/LA_A0_NODE: C1601.2, C1602.1, D1601.3, R1601.2, R1602.1, R1603.1, U1601.3
/LA port A/LA_A0_PIN: C1601.1, D1619.1, J1601.1, R1601.1
/LA port A/LA_A1_CMP: R1607.2, R1608.1, U1602.5
/LA port A/LA_A1_NODE: C1605.2, C1606.1, D1602.3, R1605.2, R1606.1, R1607.1, U1602.3
/LA port A/LA_A1_PIN: C1605.1, D1619.2, J1601.2, R1605.1
/LA port A/LA_A2_CMP: R1611.2, R1612.1, U1603.5
/LA port A/LA_A2_NODE: C1609.2, C1610.1, D1603.3, R1609.2, R1610.1, R1611.1, U1603.3
/LA port A/LA_A2_PIN: C1609.1, D1620.1, J1601.3, R1609.1
/LA port A/LA_A3_CMP: R1615.2, R1616.1, U1604.5
/LA port A/LA_A3_NODE: C1613.2, C1614.1, D1604.3, R1613.2, R1614.1, R1615.1, U1604.3
/LA port A/LA_A3_PIN: C1613.1, D1620.2, J1601.4, R1613.1
/LA port A/LA_A4_CMP: R1619.2, R1620.1, U1605.5
/LA port A/LA_A4_NODE: C1617.2, C1618.1, D1605.3, R1617.2, R1618.1, R1619.1, U1605.3
/LA port A/LA_A4_PIN: C1617.1, D1621.1, J1601.6, R1617.1
/LA port A/LA_A5_CMP: R1623.2, R1624.1, U1606.5
/LA port A/LA_A5_NODE: C1621.2, C1622.1, D1606.3, R1621.2, R1622.1, R1623.1, U1606.3
/LA port A/LA_A5_PIN: C1621.1, D1621.2, J1601.7, R1621.1
/LA port A/LA_A6_CMP: R1627.2, R1628.1, U1607.5
/LA port A/LA_A6_NODE: C1625.2, C1626.1, D1607.3, R1625.2, R1626.1, R1627.1, U1607.3
/LA port A/LA_A6_PIN: C1625.1, D1622.1, J1601.8, R1625.1
/LA port A/LA_A7_CMP: R1631.2, R1632.1, U1608.5
/LA port A/LA_A7_NODE: C1629.2, C1630.1, D1608.3, R1629.2, R1630.1, R1631.1, U1608.3
/LA port A/LA_A7_PIN: C1629.1, D1622.2, J1601.9, R1629.1
/LA port A/LA_A8_CMP: R1635.2, R1636.1, U1609.5
/LA port A/LA_A8_NODE: C1633.2, C1634.1, D1609.3, R1633.2, R1634.1, R1635.1, U1609.3
/LA port A/LA_A8_PIN: C1633.1, D1623.1, J1601.11, R1633.1
/LA port A/LA_A9_CMP: R1639.2, R1640.1, U1610.5
/LA port A/LA_A9_NODE: C1637.2, C1638.1, D1610.3, R1637.2, R1638.1, R1639.1, U1610.3
/LA port A/LA_A9_PIN: C1637.1, D1623.2, J1601.12, R1637.1
/LA port A/LA_A10_CMP: R1643.2, R1644.1, U1611.5
/LA port A/LA_A10_NODE: C1641.2, C1642.1, D1611.3, R1641.2, R1642.1, R1643.1, U1611.3
/LA port A/LA_A10_PIN: C1641.1, D1624.1, J1601.13, R1641.1
/LA port A/LA_A11_CMP: R1647.2, R1648.1, U1612.5
/LA port A/LA_A11_NODE: C1645.2, C1646.1, D1612.3, R1645.2, R1646.1, R1647.1, U1612.3
/LA port A/LA_A11_PIN: C1645.1, D1624.2, J1601.14, R1645.1
/LA port A/LA_A12_CMP: R1651.2, R1652.1, U1613.5
/LA port A/LA_A12_NODE: C1649.2, C1650.1, D1613.3, R1649.2, R1650.1, R1651.1, U1613.3
/LA port A/LA_A12_PIN: C1649.1, D1625.1, J1601.16, R1649.1
/LA port A/LA_A13_CMP: R1655.2, R1656.1, U1614.5
/LA port A/LA_A13_NODE: C1653.2, C1654.1, D1614.3, R1653.2, R1654.1, R1655.1, U1614.3
/LA port A/LA_A13_PIN: C1653.1, D1625.2, J1601.17, R1653.1
/LA port A/LA_A14_CMP: R1659.2, R1660.1, U1615.5
/LA port A/LA_A14_NODE: C1657.2, C1658.1, D1615.3, R1657.2, R1658.1, R1659.1, U1615.3
/LA port A/LA_A14_PIN: C1657.1, D1626.1, J1601.18, R1657.1
/LA port A/LA_A15_CMP: R1663.2, R1664.1, U1616.5
/LA port A/LA_A15_NODE: C1661.2, C1662.1, D1616.3, R1661.2, R1662.1, R1663.1, U1616.3
/LA port A/LA_A15_PIN: C1661.1, D1626.2, J1601.19, R1661.1
/LA port A/LA_CK_CMP: R1667.2, R1668.1, U1617.5
/LA port A/LA_CK_NODE: C1665.2, C1666.1, D1617.3, R1665.2, R1666.1, R1667.1, U1617.3
/LA port A/LA_CK_PIN: C1665.1, D1627.1, J1601.21, R1665.1
/LA port A/LA_DAC_LDAC: R1677.1, TP1601.1, U1619.4
/LA port A/LA_R2_BUS: R1602.2, R1606.2, R1610.2, R1614.2, R1618.2, R1622.2, R1626.2, R1630.2, R1634.2, R1638.2, R1642.2, R1646.2, R1650.2, R1654.2, R1658.2, R1662.2, R1666.2, R1670.2, U1620.4
/LA port A/LA_TEST_DAC: U1619.9, U1620.1
/LA port A/LA_TH_A: C1604.1, C1608.1, C1612.1, C1616.1, C1620.1, C1624.1, C1628.1, C1632.1, C1668.1, C1676.1, R1675.2, R1679.1, U1601.1, U1602.1, U1603.1, U1604.1, U1605.1, U1606.1, U1607.1, U1608.1, U1617.1
/LA port A/LA_TH_A_DAC: R1675.1, U1619.6
/LA port A/LA_TH_B: C1636.1, C1640.1, C1644.1, C1648.1, C1652.1, C1656.1, C1660.1, C1664.1, C1672.1, C1677.1, R1676.2, U1609.1, U1610.1, U1611.1, U1612.1, U1613.1, U1614.1, U1615.1, U1616.1, U1618.1
/LA port A/LA_TH_B_DAC: R1676.1, U1619.7
/LA port A/LA_TRIG_CMP: R1671.2, R1672.1, U1618.5
/LA port A/LA_TRIG_NODE: C1669.2, C1670.1, D1618.3, R1669.2, R1670.1, R1671.1, U1618.3
/LA port A/LA_TRIG_PIN: C1669.1, D1627.2, J1601.22, R1669.1
/LA port B and MIPI20/LA_B0_MID: R1701.2, R1757.1
/LA port B and MIPI20/LA_B0_NODE: D1701.3, R1701.1, R1702.1, R1703.1, U1701.4
/LA port B and MIPI20/LA_B0_PIN: J1701.1, R1757.2
/LA port B and MIPI20/LA_B1_MID: R1704.2, R1758.1
/LA port B and MIPI20/LA_B1_NODE: D1702.3, R1704.1, R1705.1, R1706.1, U1702.4
/LA port B and MIPI20/LA_B1_PIN: J1701.3, R1758.2
/LA port B and MIPI20/LA_B2_MID: R1707.2, R1759.1
/LA port B and MIPI20/LA_B2_NODE: D1703.3, R1707.1, R1708.1, R1709.1, U1703.4
/LA port B and MIPI20/LA_B2_PIN: J1701.5, R1759.2
/LA port B and MIPI20/LA_B3_MID: R1710.2, R1760.1
/LA port B and MIPI20/LA_B3_NODE: D1704.3, R1710.1, R1711.1, R1712.1, U1704.4
/LA port B and MIPI20/LA_B3_PIN: J1701.7, R1760.2
/LA port B and MIPI20/LA_B4_MID: R1713.2, R1761.1
/LA port B and MIPI20/LA_B4_NODE: D1705.3, R1713.1, R1714.1, R1715.1, U1705.4
/LA port B and MIPI20/LA_B4_PIN: J1701.9, R1761.2
/LA port B and MIPI20/LA_B5_MID: R1716.2, R1762.1
/LA port B and MIPI20/LA_B5_NODE: D1706.3, R1716.1, R1717.1, R1718.1, U1706.4
/LA port B and MIPI20/LA_B5_PIN: J1701.11, R1762.2
/LA port B and MIPI20/LA_B6_MID: R1719.2, R1763.1
/LA port B and MIPI20/LA_B6_NODE: D1707.3, R1719.1, R1720.1, R1721.1, U1707.4
/LA port B and MIPI20/LA_B6_PIN: J1701.13, R1763.2
/LA port B and MIPI20/LA_B7_MID: R1722.2, R1764.1
/LA port B and MIPI20/LA_B7_NODE: D1708.3, R1722.1, R1723.1, R1724.1, U1708.4
/LA port B and MIPI20/LA_B7_PIN: J1701.15, R1764.2
/LA port B and MIPI20/LA_B_CLAMP: C1729.1, D1701.2, D1702.2, D1703.2, D1704.2, D1705.2, D1706.2, D1707.2, D1708.2, D1709.1, Q1701.3, R1730.1, R1732.1, R1750.2
/LA port B and MIPI20/LA_B_PU_RAIL: R1702.2, R1705.2, R1708.2, R1711.2, R1714.2, R1717.2, R1720.2, R1723.2, U1715.6
/LA port B and MIPI20/LA_B_SHUNT_BASE: C1730.2, Q1701.1, R1732.2, U1717.2
/LA port B and MIPI20/LA_B_SHUNT_COL: Q1701.2, Q1701.4, R1733.1
/LA port B and MIPI20/LA_B_SHUNT_REF: C1730.1, R1730.2, R1731.1, U1717.1
/LA port B and MIPI20/MIPI_CT: C1732.2, U1716.4
/LA port B and MIPI20/MIPI_NRESET_PIN: J1702.10, Q1702.3, U1719.1
/LA port B and MIPI20/MIPI_SWCLK_B: R1742.1, U1709.4
/LA port B and MIPI20/MIPI_SWCLK_PIN: J1702.4, R1742.2, U1718.6
/LA port B and MIPI20/MIPI_SWDIO_B: R1743.1, U1710.4
/LA port B and MIPI20/MIPI_SWDIO_PIN: J1702.2, R1743.2, U1718.1
/LA port B and MIPI20/MIPI_SWO_B: R1745.1, U1712.4
/LA port B and MIPI20/MIPI_SWO_PIN: J1702.6, R1745.2, R1756.1, U1718.3
/LA port B and MIPI20/MIPI_TDI_B: R1744.1, U1711.4
/LA port B and MIPI20/MIPI_TDI_PIN: J1702.8, R1744.2, U1718.4
/LA port B and MIPI20/MIPI_TRACECLK_PIN: J1702.12, R1751.1, U1713.21, U1719.3
/LA port B and MIPI20/MIPI_TRACED0_PIN: J1702.14, R1752.1, U1713.20, U1719.4
/LA port B and MIPI20/MIPI_TRACED1_PIN: J1702.16, R1753.1, U1713.19, U1720.1
/LA port B and MIPI20/MIPI_TRACED2_PIN: J1702.18, R1754.1, U1713.18, U1720.6
/LA port B and MIPI20/MIPI_TRACED3_PIN: J1702.20, R1755.1, U1713.17, U1720.3
/LA port B and MIPI20/MIPI_VCCB: C1721.1, C1722.1, C1723.1, C1724.1, C1726.1, U1709.6, U1710.6, U1711.6, U1712.6, U1713.23, U1713.24, U1716.5, U1716.6
/LA port B and MIPI20/MIPI_VTREF: C1731.1, C1732.1, J1702.1, R1746.1, U1716.1, U1719.6
/LA port B and MIPI20/VCCIO_B_FB: R1734.2, R1735.1, R1736.1, U1714.4
/Lab PSU power/LAB_12V_FB: C1426.2, R1431.2, R1432.1, U1411.3
/Lab PSU power/LAB_12V_SW: D1405.2, L1402.2, U1411.1
/Lab PSU power/LAB_B: D1403.2, Q1414.1, Q1414.2, Q1414.3, R1416.2, R1417.1, R1457.2, U1409.3
/Lab PSU power/LAB_BOOT1: C1408.1, U1403.20
/Lab PSU power/LAB_BOOT2: C1409.1, U1403.19
/Lab PSU power/LAB_COMP: C1412.1, R1403.1, U1403.15
/Lab PSU power/LAB_COMP_RC: C1411.1, R1403.2
/Lab PSU power/LAB_CROW_D: Q1415.5, Q1415.6, Q1415.7, Q1415.8, R1458.1, R1459.1, R1460.1, R1461.1
/Lab PSU power/LAB_CROW_DRV: R1427.1, U1410.7
/Lab PSU power/LAB_CROW_G: D1408.1, Q1415.4, Q1423.4, R1427.2, R1428.1
/Lab PSU power/LAB_CROW_ISO12: C1423.1, C1436.1, C1439.1, D1417.1, R1472.2, U1410.8
/Lab PSU power/LAB_CROW_ISO_RAW: C1438.1, R1462.1, R1472.1, U1421.5
/Lab PSU power/LAB_CROW_SRC: C1423.2, C1436.2, C1438.2, C1439.2, D1408.2, D1417.2, Q1415.1, Q1415.2, Q1415.3, Q1423.1, Q1423.2, Q1423.3, R1428.2, R1462.2, U1410.5, U1410.6, U1421.4
/Lab PSU power/LAB_EN_UVLO: C1420.1, Q1403.2, R1407.1, R1408.1, U1403.1
/Lab PSU power/LAB_FSW: R1402.1, U1403.6
/Lab PSU power/LAB_HF_DRV: R1421.1, U1408.4
/Lab PSU power/LAB_HF_INN: R1419.2, U1413.4, U1418.2
/Lab PSU power/LAB_HV_GATE: Q1401.4, U1401.5
/Lab PSU power/LAB_I2C_SEL: R1447.2, U1412.1, U1416.1
/Lab PSU power/LAB_LED_GATE: Q1420.1, R1443.2, U1415.4
/Lab PSU power/LAB_LED_RAIL: Q1420.3, R1412.1, R1413.1, R1414.1, R1418.1, R1444.1, R1450.1, R1451.1
/Lab PSU power/LAB_LED_RESET_N: R1442.2, U1414.1, U1415.2
/Lab PSU power/LAB_LM_VCAP: C1401.1, U1401.1
/Lab PSU power/LAB_M_DRV: R1426.1, U1409.4
/Lab PSU power/LAB_M_G: D1403.1, Q1414.4, R1426.2, R1457.1
/Lab PSU power/LAB_M_INN: R1424.2, U1419.2, U1420.4
/Lab PSU power/LAB_P1F: F1401.2, Q1410.5, Q1410.6, Q1410.7, Q1410.8
/Lab PSU power/LAB_RANGE0_LED_A: R1450.2, U1408.1
/Lab PSU power/LAB_RANGE0_LED_G: Q1421.1, R1452.2, R1454.1
/Lab PSU power/LAB_RANGE0_LED_K: Q1421.3, U1408.2
/Lab PSU power/LAB_RANGE1_LED_A: R1451.2, U1409.1
/Lab PSU power/LAB_RANGE1_LED_G: Q1422.1, R1453.2, R1455.1
/Lab PSU power/LAB_RANGE1_LED_K: Q1422.3, U1409.2
/Lab PSU power/LAB_RANGE_M_CMD: R1453.1, U1419.4
/Lab PSU power/LAB_S1_DUMP_D: Q1424.3, R1469.2
/Lab PSU power/LAB_S1_G: D1418.1, Q1406.4, Q1407.4, R1469.1, U1404.4
/Lab PSU power/LAB_S1_LED: R1412.2, U1404.1
/Lab PSU power/LAB_S1_LED_GATE: Q1416.1, R1434.2
/Lab PSU power/LAB_S1_LED_K: Q1416.3, U1404.2
/Lab PSU power/LAB_S1_NEG_FEED: D1414.3, R1463.1
/Lab PSU power/LAB_S1_NEG_G: D1409.1, Q1424.1, R1463.2, R1466.1
/Lab PSU power/LAB_S1_SRC: D1409.2, D1418.2, Q1406.1, Q1406.2, Q1406.3, Q1407.1, Q1407.2, Q1407.3, Q1424.2, R1466.2, U1404.3
/Lab PSU power/LAB_S2_DUMP_D: Q1425.3, R1470.2
/Lab PSU power/LAB_S2_G: D1419.1, Q1408.4, Q1409.4, R1470.1, U1405.4
/Lab PSU power/LAB_S2_LED: R1413.2, U1405.1
/Lab PSU power/LAB_S2_LED_GATE: Q1417.1, R1435.2
/Lab PSU power/LAB_S2_LED_K: Q1417.3, U1405.2
/Lab PSU power/LAB_S2_NEG_FEED: D1415.3, R1464.1
/Lab PSU power/LAB_S2_NEG_G: D1410.1, Q1425.1, R1464.2, R1467.1
/Lab PSU power/LAB_S2_SRC: D1410.2, D1419.2, Q1408.1, Q1408.2, Q1408.3, Q1409.1, Q1409.2, Q1409.3, Q1425.2, R1467.2, U1405.3
/Lab PSU power/LAB_S3_DUMP_D: Q1426.3, R1471.2
/Lab PSU power/LAB_S3_G: D1420.1, Q1410.4, Q1411.4, R1471.1, U1406.4
/Lab PSU power/LAB_S3_LED: R1414.2, U1406.1
/Lab PSU power/LAB_S3_LED_GATE: Q1418.1, R1436.2
/Lab PSU power/LAB_S3_LED_K: Q1418.3, U1406.2
/Lab PSU power/LAB_S3_NEG_FEED: D1416.3, R1465.1
/Lab PSU power/LAB_S3_NEG_G: D1411.1, Q1426.1, R1465.2, R1468.1
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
